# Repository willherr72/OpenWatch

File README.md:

# OpenWatch - Open Source Smartwatch

An open-source smartwatch project developed as a school final project. This repository contains all the necessary files for building a complete smartwatch, including mechanical designs, PCB layouts, and firmware/software code.

## 📁 Project Structure

```
OpenWatch/
├── Code/                    # All code files
│   ├── Firmware/           # Embedded firmware code
│   └── Software/           # Application software code
├── KiCad/                  # PCB design files and schematics
│   ├── Smartwatch.kicad_pcb    # Main PCB layout
│   ├── Smartwatch.kicad_sch    # Main schematic
│   ├── Smartwatch.kicad_pro    # Project file
│   ├── Usermade.pretty/        # Custom component footprints
│   └── Smartwatch-backups/     # Backup files
└── Mechanical/             # 3D models and mechanical designs
    ├── Watch Assm.SLDASM       # Main assembly
    ├── Watch Body.SLDPRT       # Watch body
    ├── Watch Top.SLDPRT        # Watch top
    └── Watch PCB.SLDPRT        # PCB mechanical model
```

## 🚀 Getting Started

### Prerequisites

- **Git** - Version control system
- **KiCad** - For PCB design and schematic editing
- **SolidWorks** (or compatible CAD software) - For mechanical design files
- **Arduino IDE** - For firmware development
- **Code editor** (VSCode, Cursor, etc.) - For software development

### Installation

1. Clone this repository to your local machine
2. Install the required software listed above
3. Open the appropriate files in their respective applications

## 📚 Git Workflow Guide

**⚠️ IMPORTANT: NEVER EDIT DIRECTLY IN MASTER BRANCH! ⚠️**

All team members MUST create a branch for their work, make changes in that branch, and then merge to main. This keeps the project organized and prevents conflicts.

This section provides the essential Git commands you'll use daily. Keep it simple and follow these steps exactly.

### First Time Setup (Do this once)

#### 1. Clone the Repository
```bash
# Clone the repository to your local machine
git clone https://github.com/willherr72/OpenWatch.git

# Navigate to the project directory
cd OpenWatch
```

#### 2. Configure Git (First time only)
```bash
# Set your name and email
git config --global user.name "Your Name"
git config --global user.email "your.email@example.com"
```

## 🚀 Daily Workflow (Follow These Steps Every Time)

### Step 1: Start Your Work Session
```bash
# 1. Get the latest changes from the team
git pull origin master

# 2. Create a new branch for your work (replace 'your-feature' with what you're working on)
git checkout -b feature/your-feature

# Example: git checkout -b feature/touch-screen
# Example: git checkout -b fix/power-bug
# Example: git checkout -b docs/update-readme
```

### Step 2: Make Your Changes
```bash
# 3. Make your changes to files (edit in your code editor)
# 4. Check what files you've changed
git status

# 5. Add your changes
git add .

# 6. Save your work with a message
git commit -m "Add your feature description here"

# 7. Push your branch to GitHub
git push origin feature/your-feature
```

## 📝 Essential Commands Cheat Sheet

| What you want to do | Command |
|-------------------|---------|
| See what files changed | `git status` |
| Add all changes | `git add .` |
| Save your work | `git commit -m "Your message"` |
| Upload to GitHub | `git push origin feature/your-branch` |
| Get team's latest work | `git pull origin master` |
| Create new branch | `git checkout -b feature/your-name` |
| Switch to master | `git checkout master` |
| See all branches | `git branch` |

## ⚠️ Important Rules

1. **ALWAYS create a branch before making changes**
2. **NEVER work directly in master branch**
3. **Use descriptive branch names** (feature/touch-screen, fix/power-bug, etc.)
4. **Write clear commit messages** (what you did, not how you did it)
5. **Pull before you push** (get latest changes first)

## 🔧 Development Guidelines

### Code Organization
- **Firmware**: Place all embedded code in `Code/Firmware/`
- **Software**: Place application code in `Code/Software/`
- **Mechanical**: Keep all CAD files in `Mechanical/`
- **PCB**: All KiCad files go in `KiCad/`

### Branch Naming Examples
- `feature/touch-screen-support`
- `fix/power-management-bug`
- `docs/update-readme`
- `feature/watch-face-display`

## 🤝 Contributing

1. Create a feature branch (`git checkout -b feature/amazing-feature`)
2. Make your changes
3. Commit your changes (`git commit -m 'Add some amazing feature'`)
4. Push to the branch (`git push origin feature/amazing-feature`)
5. Merge to master following the workflow above

## 📋 Project Status

This project is currently in active development as a school final project. The repository contains:

- ✅ Basic project structure
- ✅ KiCad PCB design files
- ✅ SolidWorks mechanical models
- 🔄 Firmware development 
- 🔄 Software development 

## 📄 License

This project is open source. Please check the LICENSE file for details.

---

**Happy Coding! 🚀**

Remember: When in doubt, `git status` is your friend!

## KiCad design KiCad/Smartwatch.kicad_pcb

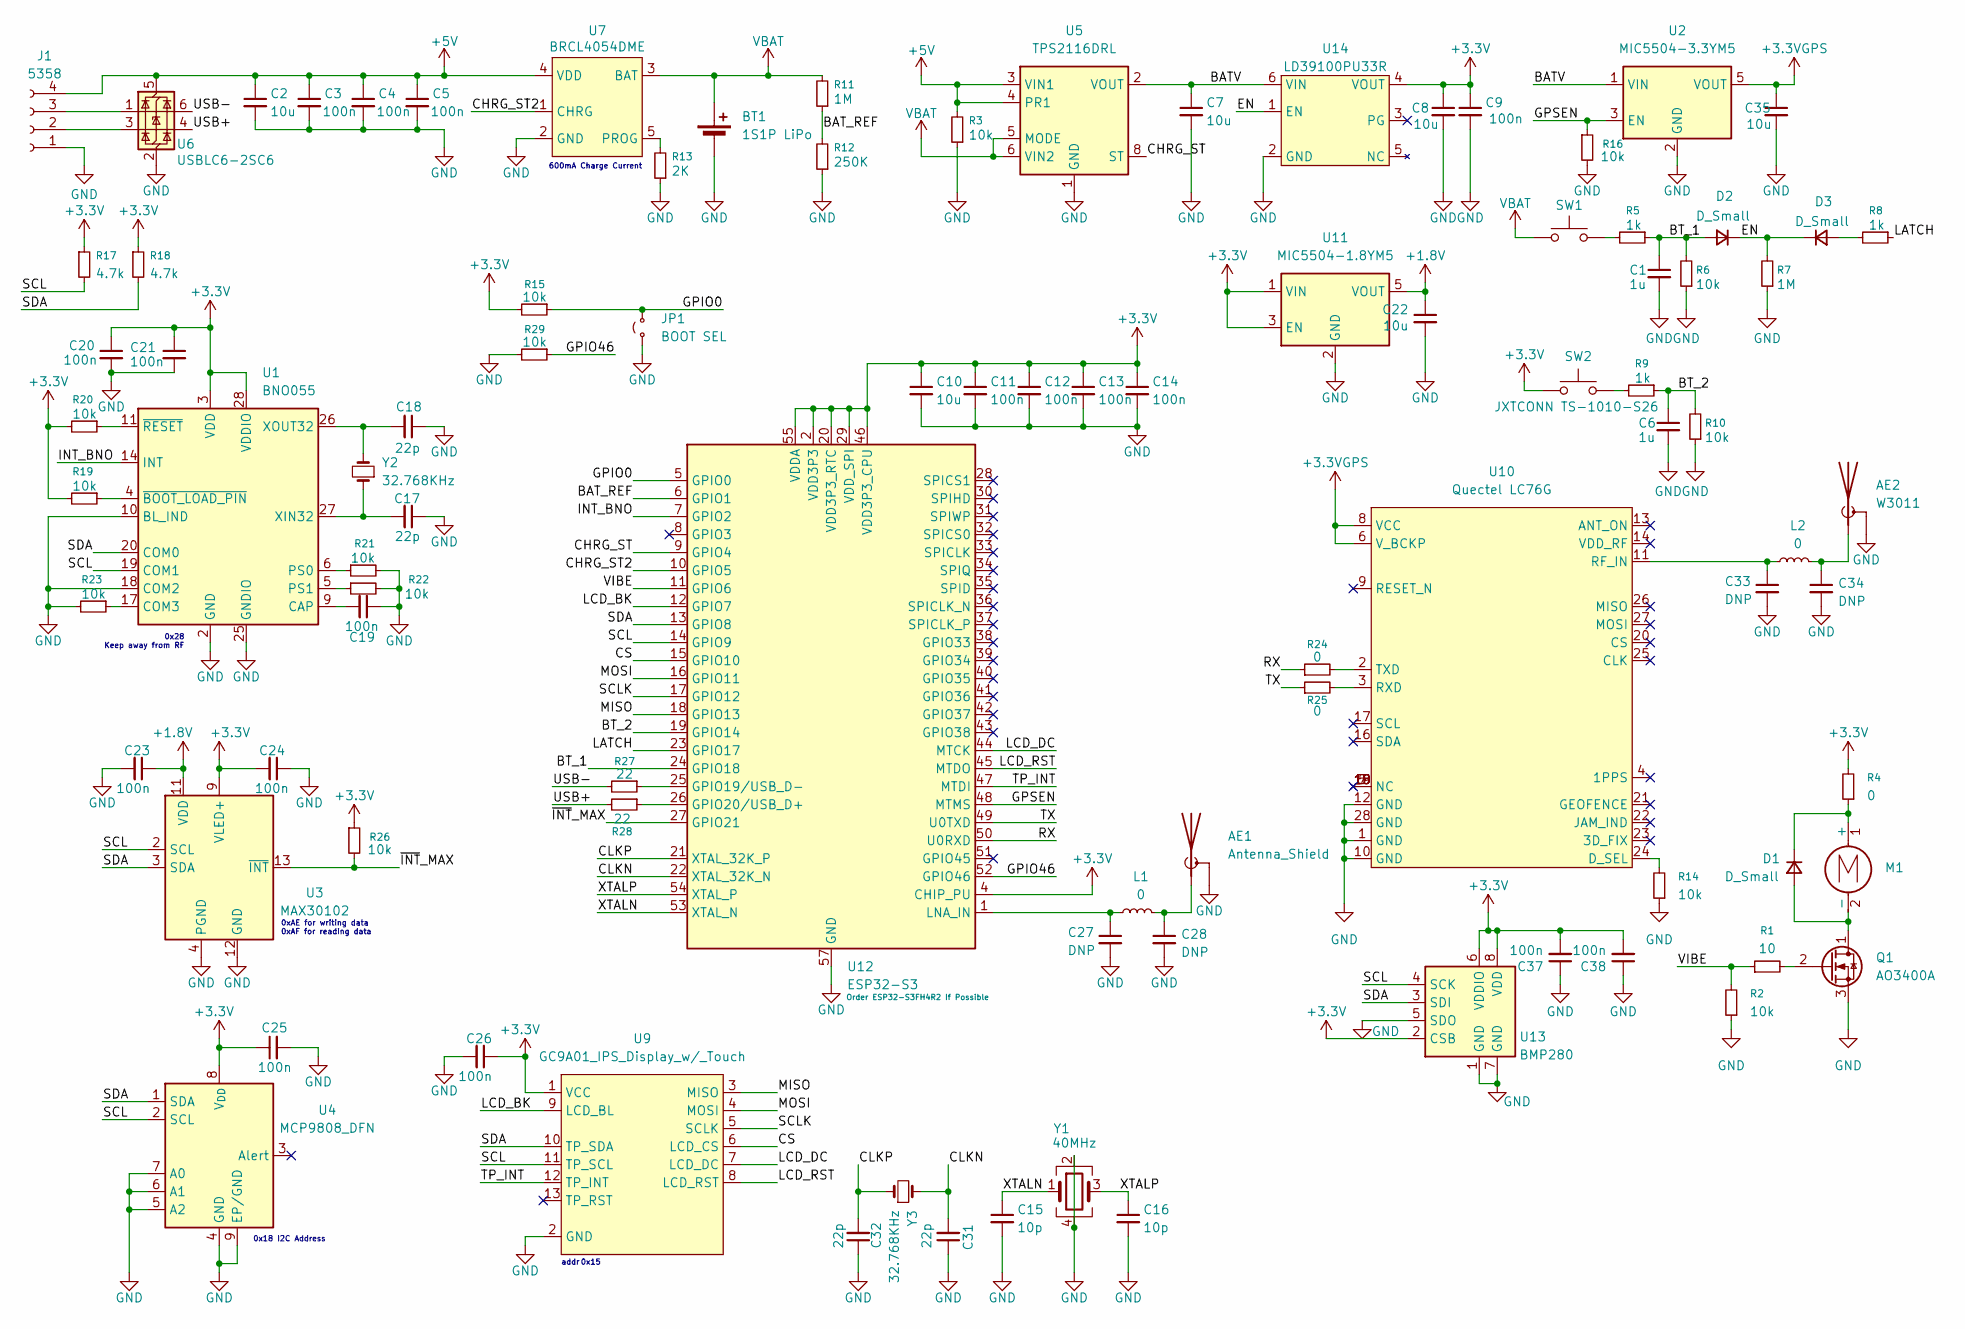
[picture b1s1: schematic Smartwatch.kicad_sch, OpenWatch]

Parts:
AE1: Antenna_Shield; L_1206_3216Metric
AE2: W3011; L_1206_3216Metric
BT1: 1S1P LiPo; PinHeader_1x02_P1.27mm_Vertical
C1, C6: 1u; C_0402_1005Metric
C2, C8, C10, C22, C35: 10u; C_0603_1608Metric
C3, C4, C5, C9, C11, C12, C13, C14, C19, C20, C21, C23, C24, C25, C26, C37, C38: 100n; C_0402_1005Metric
C7: 10u; C_0402_1005Metric
C15, C16: 10p; C_0402_1005Metric
C17, C18, C31, C32: 22p; C_0402_1005Metric
C27, C28, C33, C34: DNP; C_0402_1005Metric
D1, D2, D3: D_Small; D_SOD-323
J1: 5358; PinHeader_1x04_P2.54mm_Vertical
JP1: BOOT SEL; SolderJumper-2_P1.3mm_Open_RoundedPad1.0x1.5mm
L1, L2: 0; R_0402_1005Metric
M1: LCM1027B3605F; PinHeader_1x02_P1.27mm_Vertical
Q1: AO3400A; TSOT-23
R1: 10; R_0402_1005Metric
R2, R3, R6, R10, R14, R15, R16, R19, R20, R21, R22, R23, R26, R29: 10k; R_0402_1005Metric
R4, R24, R25: 0; R_0402_1005Metric
R5, R8, R9: 1k; R_0402_1005Metric
R7, R11: 1M; R_0402_1005Metric
R12: 250K; R_0402_1005Metric
R13: 2K; R_0402_1005Metric
R17, R18: 4.7k; R_0402_1005Metric
R27, R28: 22; R_0402_1005Metric
SW1: SW_Push; JXTCONN TS-1010-S26
SW2: JXTCONN TS-1010-S26
U1: BNO055; LGA-28_5.2x3.8mm_P0.5mm
U2: MIC5504-3.3YM5; SOT-23-5
U3: MAX30102; Maxim_OLGA-14_3.3x5.6mm_P0.8mm
U4: MCP9808_DFN; DFN-8-1EP_3x2mm_P0.5mm_EP1.7x1.4mm
U5: TPS2116DRL; SOT-583-8
U6: USBLC6-2SC6; SOT-23-6
U7: BRCL4054DME; SOT-23-5
U9: GC9A01_IPS_Display_w/_Touch; JST_ZE_B13B-ZESK-D_1x13_P1.50mm_Vertical
U10: Quectel LC76G; quectel lc76g
U11: MIC5504-1.8YM5; SOT-23-5
U12: ESP32-S3; QFN-56-1EP_7x7mm_P0.4mm_EP4x4mm
U13: BMP280; Bosch_LGA-8_2x2.5mm_P0.65mm_ClockwisePinNumbering
U14: LD39100PU33R; DFN-6-1EP_3x3mm_P0.95mm_EP1.7x2.6mm
Y1: 40MHz; Crystal_SMD_2016-4Pin_2.0x1.6mm
Y2, Y3: 32.768KHz; EPSON Q13FC13500004

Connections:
+1.8V: C22.1, C23.1, U3.11 (VDD), U11.5 (VOUT)
+3.3V: C8.1, C9.1, C10.1, C11.1, C12.1, C13.1, C14.1, C20.1, C21.1, C24.2, C25.1, C26.1, C37.2, C38.2, R4.2, R15.2, R17.1, R18.1, R19.2, R20.2, R26.1, SW2.1, U1.3 (VDD), U1.28 (VDDIO), U3.9 (VLED+), U3.10 (VLED+), U4.8 (V_{DD}), U9.1 (VCC), U11.1 (VIN), U11.3 (EN), U12.2 (VDD3P3), U12.3 (VDD3P3), U12.4 (CHIP_PU), U12.20 (VDD3P3_RTC), U12.29 (VDD_SPI), U12.46 (VDD3P3_CPU), U12.55 (VDDA), U12.56 (VDDA), U13.2 (CSB), U13.6 (VDDIO), U13.8 (VDD), U14.4 (VOUT)
+3.3VGPS: C35.1, U2.5 (VOUT), U10.6 (V_BCKP), U10.8 (VCC)
+5V: C2.1, C3.1, C4.1, C5.1, J1.4, R3.2, U5.3 (VIN1), U5.4 (PR1), U6.5 (VBUS), U7.4 (VDD)
/BATV: C7.1, U2.1 (VIN), U5.2 (VOUT), U5.7 (VOUT), U14.6 (VIN)
/BAT_REF: R11.1, R12.2, U12.6 (GPIO1)
/BT_1: C1.1, D2.2 (A), R5.1, R6.2, U12.24 (GPIO18)
/BT_2: C6.1, R9.1, R10.2, U12.19 (GPIO14)
/CHRG_ST: U5.8 (ST), U12.9 (GPIO4)
/CHRG_ST2: U7.1 (CHRG), U12.10 (GPIO5)
/CLKN: C31.2, U12.22 (XTAL_32K_N), Y3.2
/CLKP: C32.2, U12.21 (XTAL_32K_P), Y3.1
/CS: U9.6 (LCD_CS), U12.15 (GPIO10)
/EN: D2.1 (K), D3.1 (K), R7.2, U14.1 (EN)
/GPIO0: JP1.2 (B), R15.1, U12.5 (GPIO0)
/GPIO46: R29.1, U12.52 (GPIO46)
/GPSEN: R16.1, U2.3 (EN), U12.48 (MTMS)
/INT_BNO: U1.14 (INT), U12.7 (GPIO2)
/LATCH: R8.1, U12.23 (GPIO17)
/LCD_BK: U9.9 (LCD_BL), U12.12 (GPIO7)
/LCD_DC: U9.7 (LCD_DC), U12.44 (MTCK)
/LCD_RST: U9.8 (LCD_RST), U12.45 (MTDO)
/MISO: U9.3 (MISO), U12.18 (GPIO13)
/MOSI: U9.4 (MOSI), U12.16 (GPIO11)
/RX: R24.1, U12.50 (U0RXD)
/SCL: R17.2, U1.19 (COM1), U3.2 (SCL), U4.2 (SCL), U9.11 (TP_SCL), U12.14 (GPIO9), U13.4 (SCK)
/SCLK: U9.5 (SCLK), U12.17 (GPIO12)
/SDA: R18.2, U1.20 (COM0), U3.3 (SDA), U4.1 (SDA), U9.10 (TP_SDA), U12.13 (GPIO8), U13.3 (SDI)
/TP_INT: U9.12 (TP_INT), U12.47 (MTDI)
/TX: R25.1, U12.49 (U0TXD)
/USB+: R28.2, U6.4 (I/O2)
/USB-: R27.2, U6.6 (I/O1)
/VIBE: R1.1, R2.2, U12.11 (GPIO6)
/XTALN: C15.1, U12.53 (XTAL_N), Y1.1
/XTALP: C16.1, U12.54 (XTAL_P), Y1.3
/~INT_MAX: R26.2, U3.13 (~INT), U12.27 (GPIO21)
GND: AE1.2 (Shield), AE2.2 (Shield), BT1.2 (-), C1.2, C2.2, C3.2, C4.2, C5.2, C6.2, C7.2, C8.2, C9.2, C10.2, C11.2, C12.2, C13.2, C14.2, C15.2, C16.2, C17.1, C18.1, C19.1, C20.2, C21.2, C22.2, C23.2, C24.1, C25.2, C26.2, C27.2, C28.2, C31.1, C32.1, C33.2, C34.2, C35.2, C37.1, C38.1, J1.1, JP1.1 (A), Q1.3 (S), R2.1, R3.1, R6.1, R7.1, R10.1, R12.1, R13.1, R14.1, R16.2, R21.2, R22.2, R23.2, R29.2, U1.2 (GND), U1.10 (BL_IND), U1.18 (COM2), U1.25 (GNDIO), U2.2 (GND), U3.4 (PGND), U3.12 (GND), U4.4 (GND), U4.5 (A2), U4.6 (A1), U4.7 (A0), U4.9 (EP/GND), U5.1 (GND), U6.2 (GND), U7.2 (GND), U9.2 (GND), U10.1 (GND), U10.10 (GND), U10.12 (GND), U10.28 (GND), U11.2 (GND), U12.57 (GND), U13.1 (GND), U13.5 (SDO), U13.7 (GND), U14.2 (GND), Y1.2, Y1.4
unnamed: AE1.1 (A), C28.1, L1.2
unnamed: AE2.1 (A), C34.1, L2.2
unnamed: D1.2 (A), M1.2 (-), Q1.1 (D)
unnamed: D1.1 (K), M1.1 (+), R4.1
unnamed: D3.2 (A), R8.2
unnamed: J1.2, U6.3 (I/O2)
unnamed: J1.3, U6.1 (I/O1)
unnamed: Q1.2 (G), R1.2
unnamed: R5.2, SW1.2
unnamed: R9.2, SW2.2
unnamed: C19.2, U1.9 (CAP)
unnamed: R23.1, U1.17 (COM3)
unnamed: R21.1, U1.6 (PS0)
unnamed: R22.1, U1.5 (PS1)
unnamed: C17.2, U1.27 (XIN32), Y2.1
unnamed: C18.2, U1.26 (XOUT32), Y2.2
unnamed: R19.1, U1.4 (~BOOT_LOAD_PIN)
unnamed: R20.1, U1.11 (~RESET)
unnamed: R13.2, U7.5 (PROG)
unnamed: R14.2, U10.24 (D_SEL)
unnamed: C33.1, L2.1, U10.11 (RF_IN)
unnamed: R25.2, U10.3 (RXD)
unnamed: R24.2, U10.2 (TXD)
unnamed: R27.1, U12.25 (GPIO19/USB_D-)
unnamed: R28.1, U12.26 (GPIO20/USB_D+)
unnamed: C27.1, L1.1, U12.1 (LNA_IN)
VBAT: BT1.1 (+), R11.2, SW1.1, U5.5 (MODE), U5.6 (VIN2), U7.3 (BAT)

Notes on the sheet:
0x28 Keep away from RF
0x18 I2C Address
0xAE for writing data 0xAF for reading data
600mA Charge Current
addr 0x15

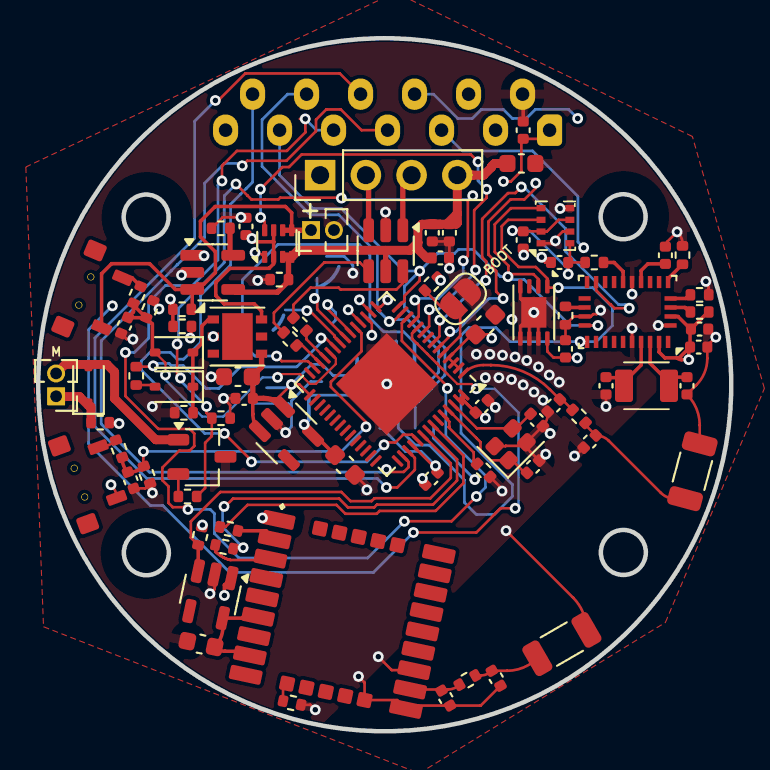
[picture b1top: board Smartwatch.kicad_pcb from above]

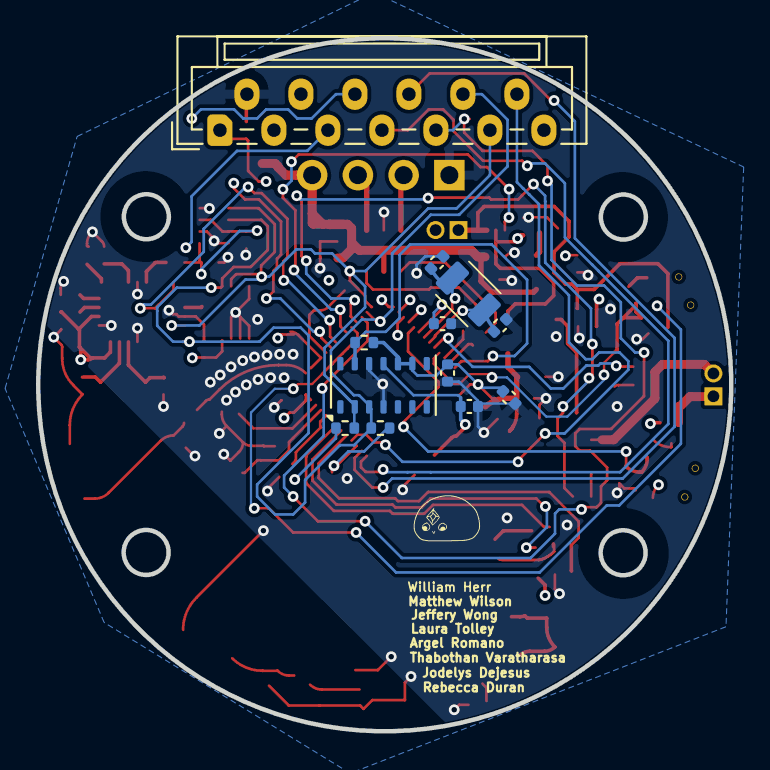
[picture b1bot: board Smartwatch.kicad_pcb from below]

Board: 4 copper layers, 38.5 x 38.5 mm, 94 parts (12 on the bottom side), 64 nets.

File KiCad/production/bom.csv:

Designator,Footprint,Quantity,Value,LCSC Part #
AE1,1206,1,Antenna_Shield,
AE2,1206,1,W3011,
BT1,PinHeader_1x02_P1.27mm_Vertical,1,1S1P LiPo,
"C1, C6",0402,2,1u,
"C10, C2, C22, C35, C8",0603,5,10u,
"C11, C12, C13, C14, C19, C20, C21, C23, C24, C25, C26, C3, C37, C38, C4, C5, C9",0402,17,100n,
"C15, C16",0402,2,10p,
"C17, C18, C31, C32",0402,4,22p,
"C27, C28, C33, C34",0402,4,DNP,
C7,0402,1,10u,
"D1, D2, D3",D_SOD-323,3,D_Small,
J1,PinHeader_1x04_P2.54mm_Vertical,1,5358,
JP1,SolderJumper-2_P1.3mm_Open_RoundedPad1.0x1.5mm,1,BOOT SEL,
"L1, L2, R24, R25, R4",0402,5,0,
M1,PinHeader_1x02_P1.27mm_Vertical,1,LCM1027B3605F,
Q1,TSOT-23,1,AO3400A,
R1,0402,1,10,
"R10, R14, R15, R16, R19, R2, R20, R21, R22, R23, R26, R29, R3, R6",0402,14,10k,
"R11, R7",0402,2,1M,
R12,0402,1,250K,
R13,0402,1,2K,
"R17, R18",0402,2,4.7k,
"R27, R28",0402,2,22,
"R5, R8, R9",0402,3,1k,
SW1,JXTCONN TS-1010-S26,1,SW_Push,
SW2,JXTCONN TS-1010-S26,1,JXTCONN TS-1010-S26,
U1,LGA-28_5.2x3.8mm_P0.5mm,1,BNO055,
U10,quectel lc76g,1,Quectel LC76G,
U11,SOT-23-5,1,MIC5504-1.8YM5,
U12,QFN-56-1EP_7x7mm_P0.4mm_EP4x4mm,1,ESP32-S3,
U13,Bosch_LGA-8_2x2.5mm_P0.65mm_ClockwisePinNumbering,1,BMP280,
U14,DFN-6-1EP_3x3mm_P0.95mm_EP1.7x2.6mm,1,LD39100PU33R,
U2,SOT-23-5,1,MIC5504-3.3YM5,
U3,Maxim_OLGA-14_3.3x5.6mm_P0.8mm,1,MAX30102,
U4,DFN-8-1EP_3x2mm_P0.5mm_EP1.7x1.4mm,1,MCP9808_DFN,
U5,SOT-583-8,1,TPS2116DRL,
U6,SOT-23-6,1,USBLC6-2SC6,
U7,SOT-23-5,1,BRCL4054DME,
U9,JST_ZE_B13B-ZESK-D_1x13_P1.50mm_Vertical,1,GC9A01_IPS_Display_w/_Touch,
Y1,Crystal_SMD_2016-4Pin_2.0x1.6mm,1,40MHz,
"Y2, Y3",EPSON Q13FC13500004,2,32.768KHz,

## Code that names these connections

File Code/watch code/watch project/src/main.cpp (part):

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Adafruit_GC9A01A tft = Adafruit_GC9A01A(&displaySPI, TFT_DC_PIN, TFT_CS_PIN, TFT_RST_PIN);

/* Button handlers */
ButtonHandler button(BUTTON_PRIMARY_PIN);        // GPIO18 - Power menu button (3-second hold)
ButtonHandler menuButton(MENU_BUTTON_PIN);      // GPIO14 - Home button (return to watch face)

/* GPIO18 power menu state tracking */
unsigned long gpio18_press_start = 0;
bool gpio18_pressed = false;
bool power_menu_shown = false;
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    return 87;  // Spoofed battery percentage
    
    // ORIGINAL CODE COMMENTED OUT FOR VIDEO:
    // // Read ADC value from GPIO1
    // int adcValue = analogRead(BATTERY_ADC_PIN);
    // 
    // // Convert ADC value to voltage
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    }
    if (devicesFound == 0) {
        Serial.println(F("  ✗ NO I2C devices found!"));
        Serial.println(F("  Check connections: SDA=8, SCL=9, Power=GPIO17"));
    } else {
        Serial.printf("  Found %d I2C device(s)\n", devicesFound);
    }
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    Serial.println(F("Menu button initialized"));
    Serial.flush();
    
    /* GPIO14 is MENU_BUTTON_PIN (already initialized above as menuButton) */
    /* GPIO18 is BUTTON_PRIMARY_PIN (already initialized above as button) */
    /* GPIO18 power button functionality added in loop */
    Serial.printf("GPIO14 (Menu/Home) and GPIO18 (Primary/Power) configured\n");
    
    Serial.printf("Initial button states - Primary (GPIO %d): %d, Menu (GPIO %d): %d\n", 
        BUTTON_PRIMARY_PIN, digitalRead(BUTTON_PRIMARY_PIN), 
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                      menuEvent == ButtonEvent::SHORT_PRESS ? "SHORT" : "LONG");
    }

    /* Long press primary button -> removed (GPIO18 now used for power menu) */
    // Sleep function removed from GPIO18
    
    /* Menu button (GPIO14) functionality moved above to return to watch face */
    /* WiFi toggle functionality removed to use GPIO14 as home button */
    
    /* ============================================
     * GPIO14 - Home button (return to watch face)
     * Note: GPIO14 is MENU_BUTTON_PIN, so we use the menuButton short press
     * ============================================ */
    if (menuEvent == ButtonEvent::SHORT_PRESS) {
        // GPIO14 short press returns to watch face from any menu
        if (app_manager_get_current() != AppType::WATCH_FACE && app_manager_get_current() != AppType::POWER_MENU) {
            Serial.println(F("[GPIO14] Menu button - returning to watch face"));
            app_manager_return_home();
        }
    }
    
    /* ============================================
     * GPIO18 - Power menu button (3-second hold)
     * Using ButtonHandler for better debouncing
     * ============================================ */
    bool gpio18_current = button.isButtonPressed();
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        gpio18_pressed = true;
        gpio18_press_start = now;
        power_menu_shown = false;
        Serial.println(F("[GPIO18] Power button pressed - waiting for 3 seconds..."));
    } else if (!gpio18_current && gpio18_pressed) {
        // Button released
        gpio18_pressed = false;
        power_menu_shown = false;
        Serial.println(F("[GPIO18] Power button released"));
    } else if (gpio18_current && gpio18_pressed && !power_menu_shown && (now - gpio18_press_start >= 3000)) {
        // Held for 3 seconds
        power_menu_shown = true;
        Serial.println(F("[GPIO18] Power button held for 3 seconds - showing power menu"));
        app_manager_navigate_to(AppType::POWER_MENU);
    }
    
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
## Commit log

2025-09-04 init commit
2025-09-04 Added KiCad files
2025-09-05 PCB V1
2025-09-06 minor updates - practice pulling to local branch
2025-09-07 AAAAAAAAAAAAAAAAA
2025-09-29 rev 5?
2025-09-29 added teardrops, cleaned up a few traces
2025-09-30 docs: Add comprehensive README with Git workflow guide
    - Created detailed README for OpenWatch smartwatch project
    - Added complete Git workflow instructions for team collaboration
    - Included project structure documentation
    - Added development guidelines and commit conventions
    - Removed empty Electrical folder
    - Updated prerequisites to include Cursor editor
2025-09-30 forgot to add files oops
2025-09-30 docs: Simplify Git workflow and emphasize branch-only development
    - Added clear warning about never editing master directly
    - Simplified Git workflow to essential daily commands only
    - Created step-by-step daily workflow guide
    - Added essential commands cheat sheet table
    - Removed complex advanced Git commands to avoid confusion
    - Updated contributing guidelines to match simplified workflow
2025-09-30 last update I promise
2025-10-01 gonna jump off a builing on facebook live
2025-10-01 cenetered charging pins?
2025-10-03 changed up PCB design, still WIP
2025-10-04 moved part around
2025-10-04 basic firmware
2025-10-04 simplified code and added comments
2025-10-05 a lot of pcb updates, more to come
2025-10-05 final traces hopfully
2025-10-06 final version of pcb
2025-10-06 uploaded final pcb
2025-10-06 fixing github
2025-10-06 fixed kicad files
2025-10-07 Names Added
2025-10-07 prepared for production
2025-10-10 Working display driver and graphical UI elements
2025-10-12 added pin diagram to code
2025-10-13 added touch functionality and minor bug fixes
2025-10-19 Improved guesture controlls and no wifi handling
2025-10-19 Improved guesture controls and no wifi handling
2025-10-20 Better gesture controls and simplified gpio mapping
2025-10-20 removed wifi pass
2025-10-22 Changed board to esp32 S3 and pin definitions
2025-10-28 Programming settings for esp32 s3
2025-10-29 Restore point for mostly working wifi
2025-10-30 updated wifi driver
2025-11-03 Working wifi
2025-11-03 codes for py to labiview and GPS for labview
2025-11-10 WIP: LVGL migration - mid-transition state
2025-11-10 Complete LVGL migration - remove all old display code
    - Deleted old display system (app_manager, clock_display, display_adapter)
    - Removed old app implementations (calibration, fitness, timer, weather, wifi_app, altimeter)
    - Removed old touch system (touch_handler, touch_input)
    - Integrated CST816S touch driver directly into lvgl_touch
    - Cleaned up duplicate lv_conf.h files
    - Fixed merge conflict in main.cpp
2025-11-10 Fix LVGL build - exclude ARM-specific assembly code
    - Added extra_script.py to filter out ARM Helium/NEON assembly files
    - Updated lv_conf.h to explicitly disable ARM hardware acceleration
    - Added build_unflags to remove ARM architecture defines
    - Added ESP32-specific build flags to prevent ARM code inclusion
    This fixes compilation errors where LVGL was trying to compile ARM assembly on ESP32-S3 (Xtensa)
2025-11-10 Downgrade LVGL to 8.3.11 and update API compatibility
    - Downgraded from LVGL 9.2 to 8.3.11 to avoid ARM assembly issues
    - Updated lvgl_display.cpp to use LVGL 8.3 API (lv_disp_drv_t)
    - Updated lvgl_touch.cpp to use LVGL 8.3 API (lv_indev_drv_t)
    - Fixed lv_refr_now() calls to use NULL parameter
    - LVGL 8.3 is more stable and doesn't include ARM Helium/NEON code
2025-11-10 Fix Adafruit BusIO BitOrder issue with library patching
    Root cause: ESP32 Arduino framework 3.x removed BitOrder enum, but
    Adafruit BusIO library still references it.
    Solution: Created extra_script.py that patches the BusIO library after
    download by injecting BitOrder typedef directly into Adafruit_SPIDevice.h
    This is more reliable than forced includes since it modifies the library
    source before compilation.
2025-11-12 swapped all code to lvgl, still wip
2025-11-13 added sensor streaming and compass
2025-11-17 added battery monitoring
2025-11-17 added huge_app and constant com streaming
2025-11-18 added ble, weather, step counter, vibe, timer, gps, and more -- firmware 1.0.0 complete
2025-11-18 added new velco wrist band
2025-11-18 added watch2fpga, allowing com streaming to FPGA
2025-11-19 Verilog/fpga
2025-11-24 Add spoofed data for video demo - GPS, steps, compass, heart rate, battery, weather
2025-11-24 final updates for watch2fpga
2025-12-01 final fpga code
